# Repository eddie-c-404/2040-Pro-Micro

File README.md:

# 2040-Pro-Micro
An open source Arduino Pro Micro but with an RP2040.

**Overview:**

The Arduino Pro Micro is a small-form-factor, useful, and pretty cool microcontroller that's missing just one thing: some more juice!!! Unfortunately, it only runs at 16 MHz and is an 8-bit CPU. Introducing the RP2040 Pro Micro, it's just like the Arduino in every single way, but it includes some more powerful components and better specs. This project originates from a problem I had a while ago. 11-year-old me had just made his finest electronics project, A flight control stick to play flight sims on his MacBook (IDK why, but I really enjoyed those back then). He had started with an Arduino Nano, and after a couple of hours of wiring and searching for how to code, he arrived at his final step: testing it. As you might be able to tell, it didn't work at all. Matter of fact, he spent more time trying to get it to work than he spent building it. He googled and googled and learned about HID, and how the ATmega 328P doesn't have that. So, unfortunately, all other solutions were out of his budget, so he moved on to blinking LEDs. Now, 3 years later, I created this to be a substitute for the heavily underpowered Arduino Pro Micro and to achieve my goal of creating a flight stick (ig).    

**Specs:**

*CPU:* RP2040 featuring dual ARM Cortex-M0+ (32-bit ARMv6-M) cores running at 133 MHz, 264 KB of internal SRAM.

*Flash:* 64 Mbit (8 MB) of external flash NOR Memory IC

*Connectivity:* USB-C port supporting up to USB 2.0 speeds for data transfer.

*I/O:* 24 pins with 20 I/O pins and 4 power pins. (Note that pins do **NOT** have +5v tolerence).

*Buttons:*  BOOT SELECT button, RESET button.

*Power:* USB-C for +5v input, MCP1700xx LDO for voltage regulation (+3.3v), max 250 mA output overall.

**BOM and other pictures:**

| Name         | Reference on pcb | LCSC Part # | Footprint     | Price |
|--------------|------------------|-------------|---------------|-------|
| 1uF          | C1/C12           | C15849      | C0603         | 0.39  |
| 0.1uF        | C2-C11/C18/C17   | C60474      | C0402         | 0.1   |
| 10uF         | C13/C14          | C19702      | C0603         | 0.4   |
| 33pF         | C15/C16          | C70465      | C0402         | 0.36  |
| USB-C        | J1               | C165948     | SMD           | 0.85  |
| GPIO pins    | J2/J3            | C6332195    | 1x12          | 0.4   |
| SWD pins     | J4               | C32713269   | 1x03          | 0.11  |
| Crystal      | Y1               | C9002       | SMD3225-4P    | 0.73  |
| Buttons      | SW1/SW2          | C720477     | SMD,4x3mm     | 0.55  |
| 10k          | R6/R8            | C98220      | R0603         | 0.15  |
| 5.1k         | R1/R2            | C2907044    | R0603         | 0.12  |
| 27ohm        | R3/R4            | C2907021    | R0603         | 0.1   |
| 1k           | R5/R7            | C22548      | R0603         | 0.15  |
| RP2040       | U1               | C2040       | LQFN-56(7x7)  | 0.95  |
| MCP1700xx    | U2               | C39051      | SOT-23        | 1.88  |
| W25Q64JVSSIQ | U3               | C97521      | SOIC-8-208mil | 1.65  |
| Total        | X                | X           | X             | 8.89  |

**General Insruction:**

If you would like to get this PCB manufactured, you can download the rp2040_pro_micro.zip file. When your pcb manufacturer asks for a gerber file, upload that.
If you would like to copy the schematic, you can but take note that the pins labled left pins are the rigth pins and vice versa.
The BOM file is the BOM.csv, the CPL file is positions.csv.
If you want to use the already existing kicad files, you can use the .kicad_pro (entire proj.), the .kicad_sch (schematic), or the .kicad_pcb (the pcb).

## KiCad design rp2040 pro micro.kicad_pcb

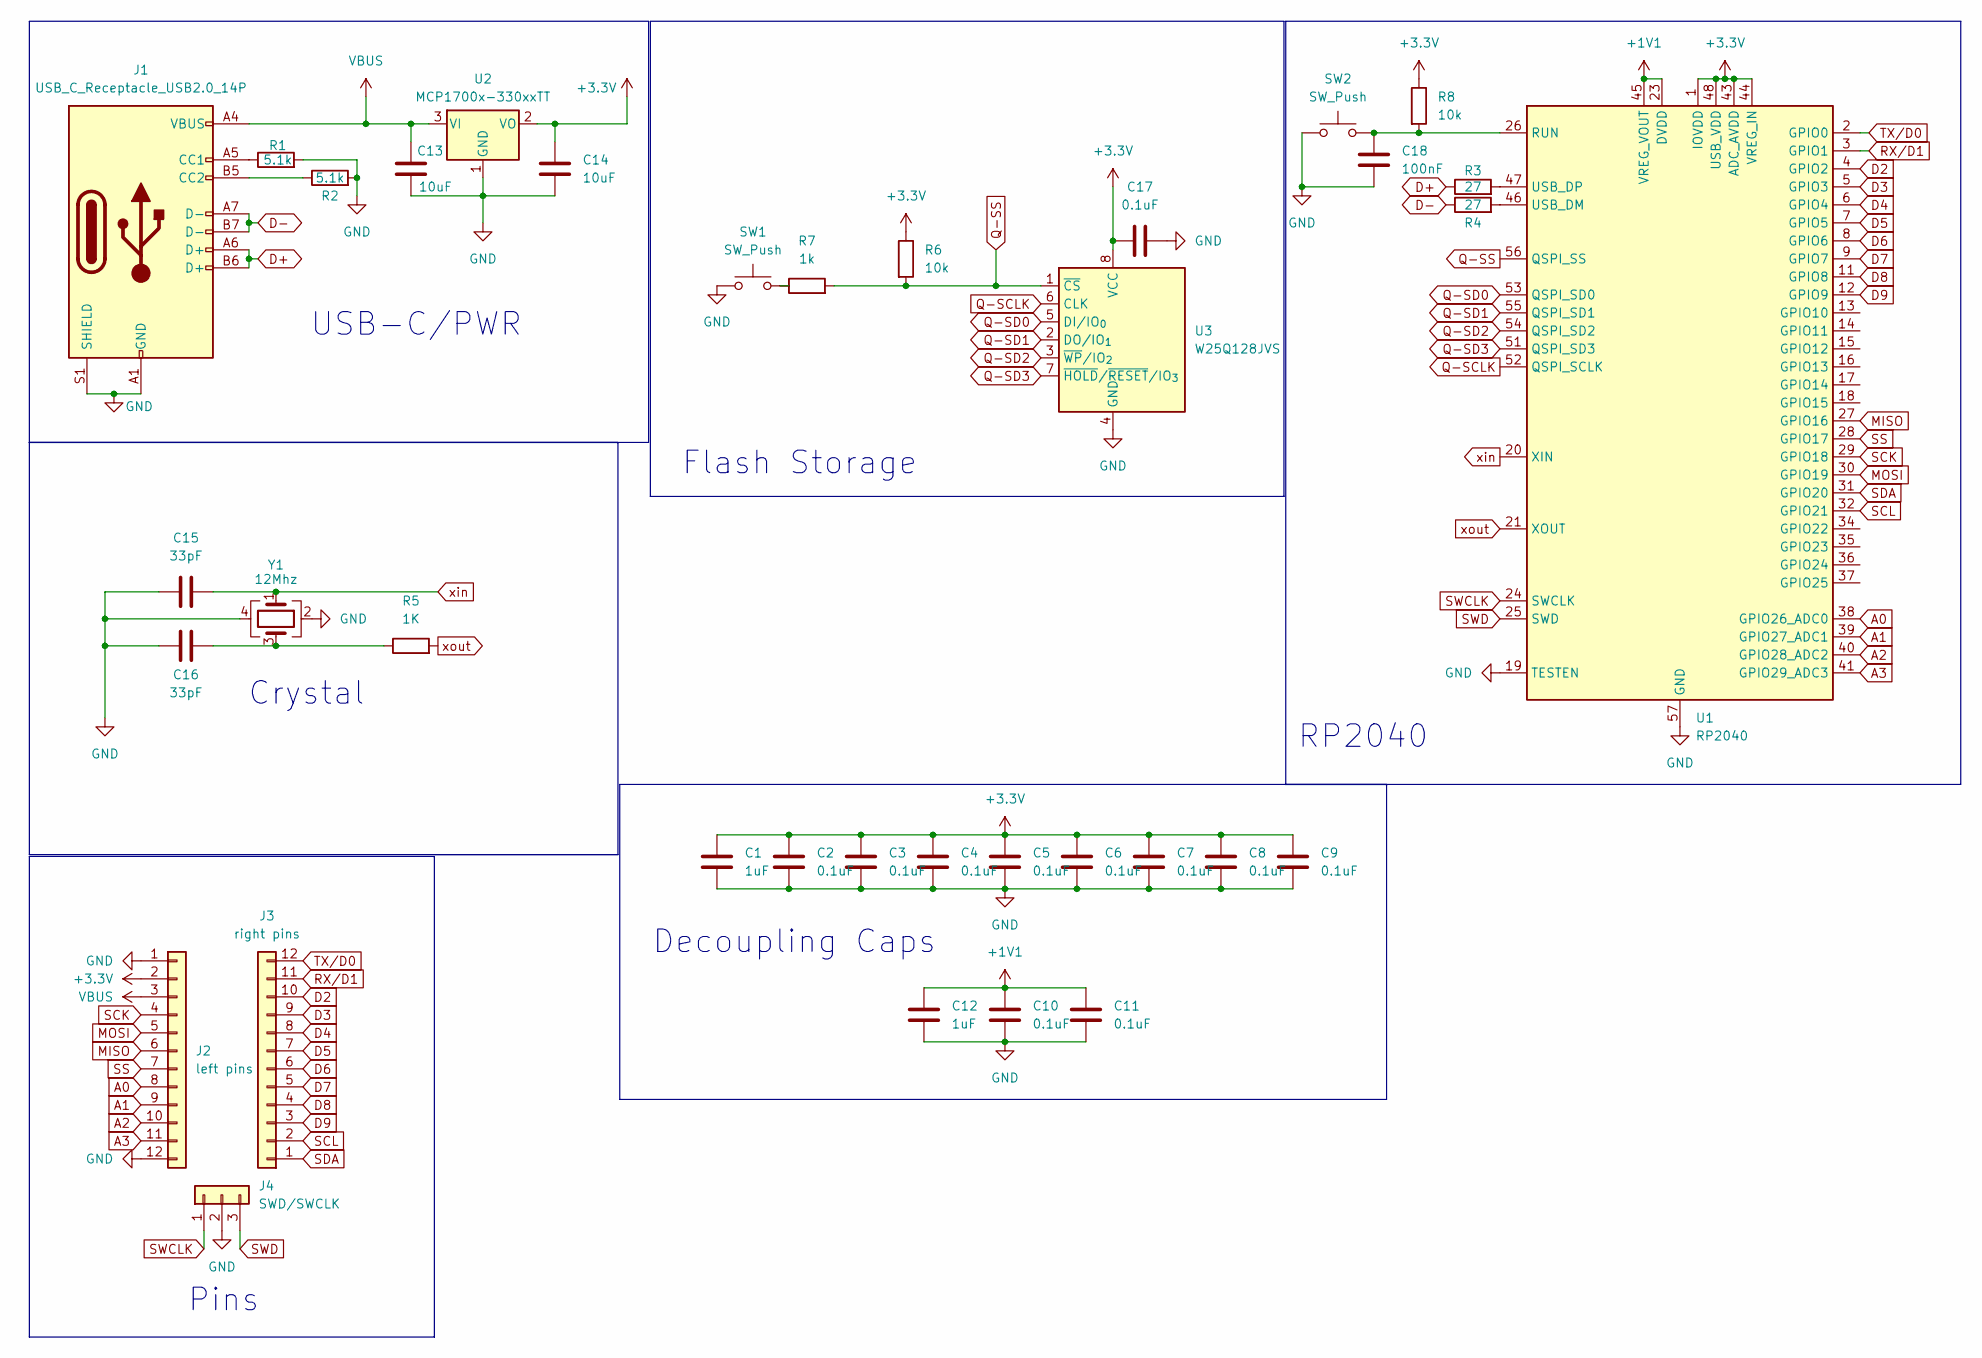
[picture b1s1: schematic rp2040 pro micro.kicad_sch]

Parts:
C1, C12: 1uF; C_0603_1608Metric
C2, C3, C4, C5, C6, C7, C8, C9, C10, C11, C17: 0.1uF; C_01005_0402Metric
C13, C14: 10uF; C_0603_1608Metric
C15, C16: 33pF; C_01005_0402Metric
C18: 100nF; C_01005_0402Metric
J1: USB_C_Receptacle_USB2.0_14P; USB_C_Receptacle_HRO_TYPE-C-31-M-12
J2: left pins; PinHeader_1x12_P2.54mm_Vertical
J3: right pins; PinHeader_1x12_P2.54mm_Vertical
J4: SWD/SWCLK; PinHeader_1x03_P2.54mm_Vertical
R1, R2: 5.1k; R_0603_1608Metric
R3, R4: 27; R_0603_1608Metric
R5: 1K; R_0603_1608Metric
R6, R8: 10k; R_0603_1608Metric
R7: 1k; R_0603_1608Metric
SW1, SW2: SW_Push; SW_Push_SPST_NO_Alps_SKRK
U1: RP2040; QFN-56-1EP_7x7mm_P0.4mm_EP3.2x3.2mm
U2: MCP1700x-330xxTT; SOT-23
U3: W25Q128JVS; SOIC-8_5.3x5.3mm_P1.27mm
Y1: 12Mhz; Crystal_SMD_3225-4Pin_3.2x2.5mm

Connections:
+1V1: C10.1, C11.1, C12.1, U1.23 (DVDD), U1.45 (VREG_VOUT), U1.50 (DVDD)
+3.3V: C1.1, C2.1, C3.1, C4.1, C5.1, C6.1, C7.1, C8.1, C9.1, C14.1, C17.1, J2.2, R6.1, R8.1, U1.1 (IOVDD), U1.10 (IOVDD), U1.22 (IOVDD), U1.33 (IOVDD), U1.42 (IOVDD), U1.43 (ADC_AVDD), U1.44 (VREG_IN), U1.48 (USB_VDD), U1.49 (IOVDD), U2.2 (VO), U3.8 (VCC)
A0: J2.8, U1.38 (GPIO26_ADC0)
A1: J2.9, U1.39 (GPIO27_ADC1)
A2: J2.10, U1.40 (GPIO28_ADC2)
A3: J2.11, U1.41 (GPIO29_ADC3)
D2: J3.10, U1.4 (GPIO2)
D3: J3.9, U1.5 (GPIO3)
D4: J3.8, U1.6 (GPIO4)
D5: J3.7, U1.7 (GPIO5)
D6: J3.6, U1.8 (GPIO6)
D7: J3.5, U1.9 (GPIO7)
D8: J3.4, U1.11 (GPIO8)
D9: J3.3, U1.12 (GPIO9)
D+: J1.A6 (D+), J1.B6 (D+), R3.1
D-: J1.A7 (D-), J1.B7 (D-), R4.1
GND: C1.2, C2.2, C3.2, C4.2, C5.2, C6.2, C7.2, C8.2, C9.2, C10.2, C11.2, C12.2, C13.2, C14.2, C15.2, C16.2, C17.2, C18.2, J1.A1 (GND), J1.A12 (GND), J1.B1 (GND), J1.B12 (GND), J1.S1 (SHIELD), J2.1, J2.12, J4.2, R1.2, R2.2, SW1.1, SW2.1, U1.19 (TESTEN), U1.57 (GND), U2.1 (GND), U3.4 (GND), Y1.2, Y1.4; also elsewhere on the board
MISO: J2.6, U1.27 (GPIO16)
MOSI: J2.5, U1.30 (GPIO19)
unnamed: C16.1, R5.1, Y1.3
unnamed: J1.A5 (CC1), R1.1
unnamed: J1.B5 (CC2), R2.1
unnamed 22: R7.1, SW1.2; also elsewhere on the board
unnamed 23: C18.1, R8.2, SW2.2, U1.26 (RUN); also elsewhere on the board
unnamed: R4.2, U1.46 (USB_DM)
unnamed: R3.2, U1.47 (USB_DP)
Q-SCLK: U1.52 (QSPI_SCLK), U3.6 (CLK)
Q-SD0: U1.53 (QSPI_SD0), U3.5 (DI/IO_{0})
Q-SD1: U1.55 (QSPI_SD1), U3.2 (DO/IO_{1})
Q-SD2: U1.54 (QSPI_SD2), U3.3 (~WP/IO_{2})
Q-SD3: U1.51 (QSPI_SD3), U3.7 (~HOLD/~RESET/IO_{3})
Q-SS: R6.2, R7.2, U1.56 (QSPI_SS), U3.1 (~CS)
RX/D1: J3.11, U1.3 (GPIO1)
SCK: J2.4, U1.29 (GPIO18)
SCL: J3.2, U1.32 (GPIO21)
SDA: J3.1, U1.31 (GPIO20)
SS: J2.7, U1.28 (GPIO17)
SWCLK: J4.1, U1.24 (SWCLK)
SWD: J4.3, U1.25 (SWD)
TX/D0: J3.12, U1.2 (GPIO0)
VBUS: C13.1, J1.A4 (VBUS), J1.A9 (VBUS), J1.B4 (VBUS), J1.B9 (VBUS), J2.3, U2.3 (VI)
xin: C15.1, U1.20 (XIN), Y1.1
xout: R5.2, U1.21 (XOUT)

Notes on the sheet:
USB-C/PWR
Decoupling Caps
Crystal
RP2040
Flash Storage
Pins

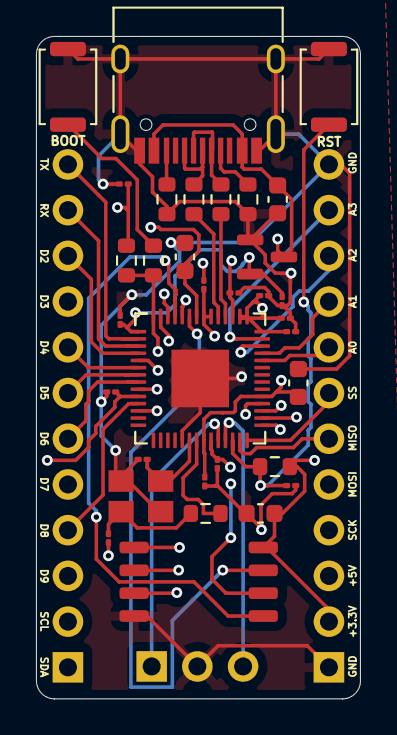
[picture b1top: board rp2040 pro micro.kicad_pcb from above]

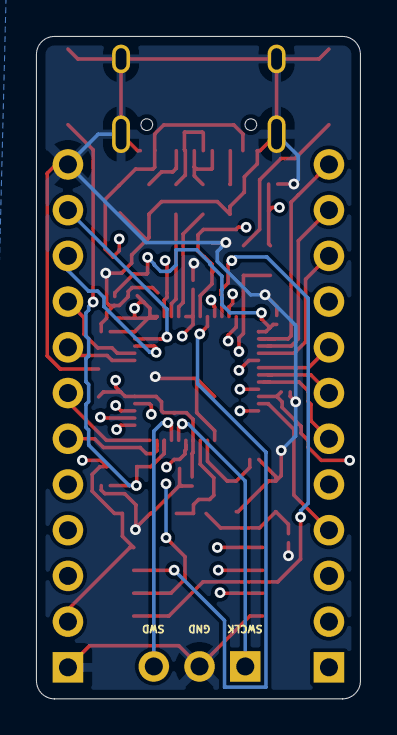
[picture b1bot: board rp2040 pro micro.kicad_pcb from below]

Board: 4 copper layers, 18.0 x 36.8 mm, 36 parts (2 on the bottom side), 43 nets.

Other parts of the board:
BOOT: SW_Push; SW_Push_SPST_NO_Alps_SKRK
RST: SW_Push; SW_Push_SPST_NO_Alps_SKRK

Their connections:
GND: BOOT.1, RST.1; also elsewhere on the board
unnamed 22: BOOT.2; also elsewhere on the board
unnamed 23: RST.2; also elsewhere on the board

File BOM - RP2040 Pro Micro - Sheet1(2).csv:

Name,Reference on pcb,LCSC Part #,Footprint,Link,Price,Amount
1uF,C1/C12,C15849,C0603,link,0.39,2
0.1uF,C2-C11/C18/C17,C60474,C0402,link,0.1,12
10uF,C13/C14,C19702,C0603,link,0.4,2
33pF,C15/C16,C70465,C0402,link,0.36,2
USB-C,J1,C165948,SMD,link,0.85,1
pins,J2/J3,C6332195,1x12,link,0.4,2
other pins,J4,C32713269,1x03,link,0.11,1
crystal,Y1,C9002,SMD3225-4P,link,0.73,1
buttons,SW1/SW2,C720477,"SMD,4x3mm",link,0.55,2
10k,R6/R8,C98220,R0603,link,0.15,2
5.1k,R1/R2,C2907044,R0603,link,0.12,2
27ohm,R3/R4,C2907021,R0603,link,0.1,2
1k,R5/R7,C22548,R0603,link,0.15,2
RP2040,U1,C2040,LQFN-56(7x7),link,0.95,1
MCP1700xx,U2,C39051,SOT-23,link,1.88,1
W25Q64JVSSIQ,U3,C97521,SOIC-8-208mil,link,1.65,1
Total,X,X,X,X,8.89,X
